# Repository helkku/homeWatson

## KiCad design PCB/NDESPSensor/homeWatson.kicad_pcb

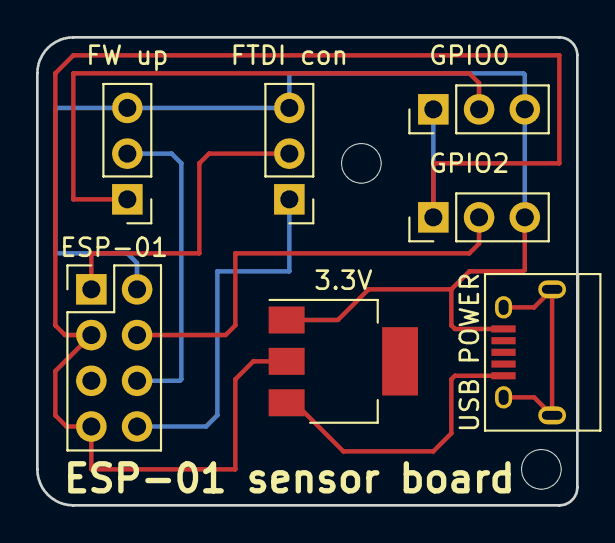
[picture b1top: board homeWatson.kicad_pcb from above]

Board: 2 copper layers, 30.0 x 26.0 mm, 7 parts (0 on the bottom side), 8 nets.

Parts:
3.3V: LD1117S33CTR; SOT-223
ESP-01: CONN_02X04; Pin_Header_Straight_2x04_Pitch2.54mm
FTDI con: CONN_01X03; Pin_Header_Straight_1x03_Pitch2.54mm
FW up: CONN_01X03; Pin_Header_Straight_1x03_Pitch2.54mm
GPIO0, GPIO2: CONN_01X03; Pin_Header_Straight_1x03_Pitch2.54mm
USB POWER: USB_OTG; USB_Micro-B

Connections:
unnamed: 3.3V.3, USB POWER.1
unnamed: 3.3V.1, ESP-01.2, FTDI con.3, FW up.3, GPIO0.3, GPIO2.3, USB POWER.5
unnamed: ESP-01.1, FTDI con.2
unnamed: 3.3V.2, ESP-01.3, ESP-01.7, GPIO0.1, GPIO2.1
unnamed: ESP-01.4, GPIO2.2
unnamed: ESP-01.6, FW up.2
unnamed: ESP-01.8, FTDI con.1
unnamed: FW up.1, GPIO0.2

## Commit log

2018-02-17 PCB and ESP sensor server code
